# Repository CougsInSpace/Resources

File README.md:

# Getting Involved with Cougs in Space #
Cougs in Space is currently developing its first nanosatellite, **CougSat-1**, at Washington State University.

## Step One: Nanosatellites ##
* Read [Wikipedia](https://en.wikipedia.org/wiki/CubeSat)
* Read [NASA's CubeSat 101](https://github.com/CougsInSpace/Resources/blob/master/Subsystems/General/NASACubeSat101.pdf)
* Read the [CubeSat Specifications](https://github.com/CougsInSpace/Resources/blob/master/CubeSatSpecifications/CubeSatDesignSpecificationRev13.pdf)

## Step Two: Find a Team ##
Our [website](https://cis.vcea.wsu.edu/our-teams/) describes each sub team's roles. Find one that is interesting that you want to join and [let us know](https://cis.vcea.wsu.edu/new-member-application-form/).

## Step Three: Join Github ##
Don't know what Github is? [Learn here](https://guides.github.com/activities/hello-world/)

## Step Four: Check out our SOPs ##
These are the standard operating procedures within Cougs in Space:
* [Acronyms](https://github.com/CougsInSpace/Resources/blob/master/StandardOperatingProcedures/Acronyms.pdf)
* [Coding conventions](https://github.com/CougsInSpace/Resources/blob/master/StandardOperatingProcedures/Code.pdf)
* [Github](https://github.com/CougsInSpace/Resources/blob/master/StandardOperatingProcedures/GitHub.pdf)
* [Project Management](https://github.com/CougsInSpace/Resources/blob/master/StandardOperatingProcedures/ProjectManagement.pdf)
* [Units](https://github.com/CougsInSpace/Resources/blob/master/StandardOperatingProcedures/Units.pdf)

## Step Five: Start Working ##
All of our design files are located at [https://github.com/CougsInSpace](https://github.com/CougsInSpace).

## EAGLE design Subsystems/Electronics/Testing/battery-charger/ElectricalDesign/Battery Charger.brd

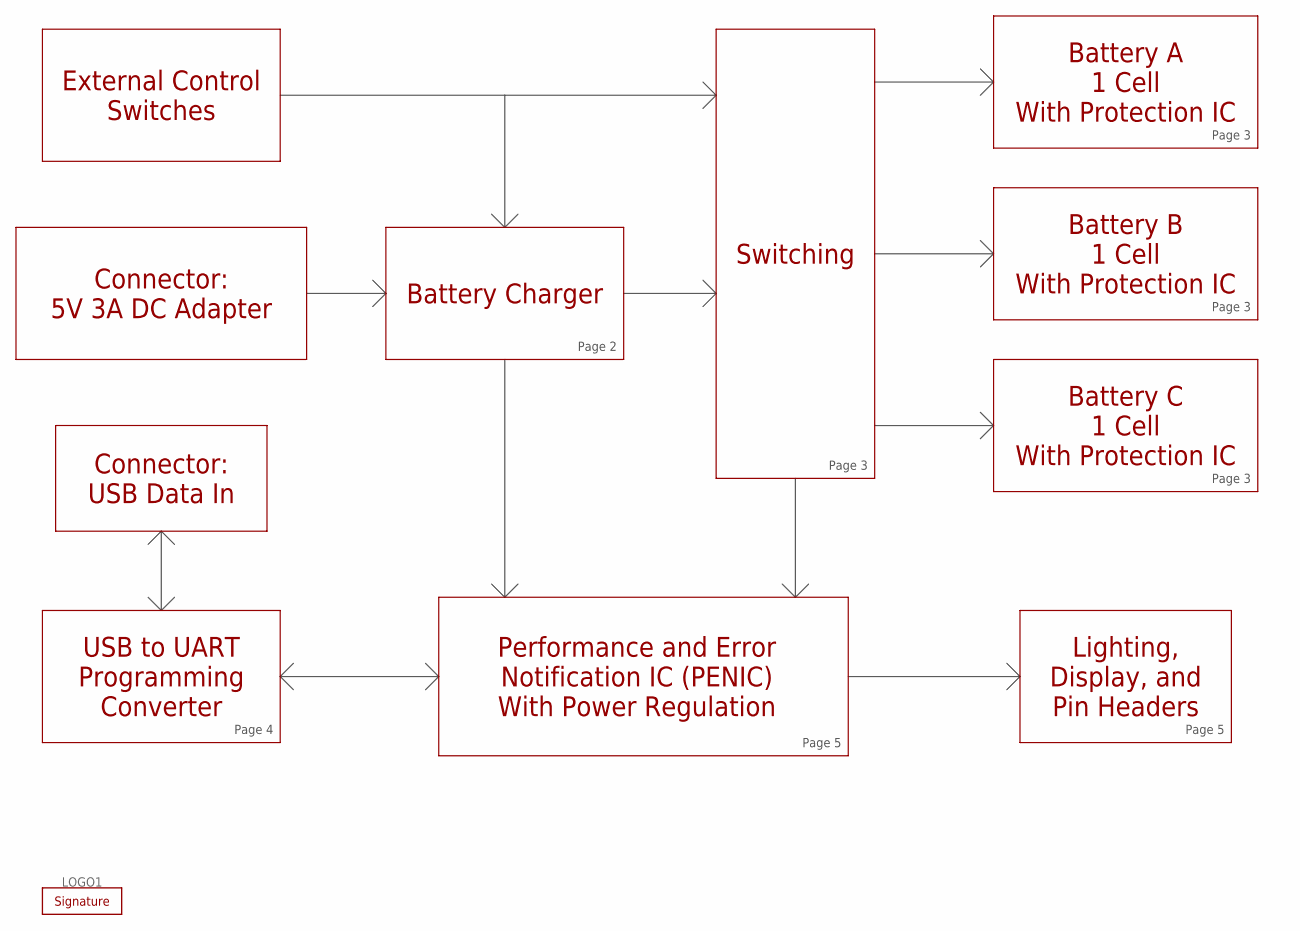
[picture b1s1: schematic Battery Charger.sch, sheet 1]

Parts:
LOGO1: SIGNATUREZACHARY; SIGN-ZACHARY

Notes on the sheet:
Connector: 5V 3A DC Adapter
Battery Charger
Switching
Battery A 1 Cell With Protection IC
Battery B 1 Cell With Protection IC
Battery C 1 Cell With Protection IC
Page 2
Page 3
Performance and Error Notification IC (PENIC) With Power Regulation
Lighting, Display, and Pin Headers
Page 5
Connector: USB Data In
USB to UART Programming Converter
Page 4
External Control Switches

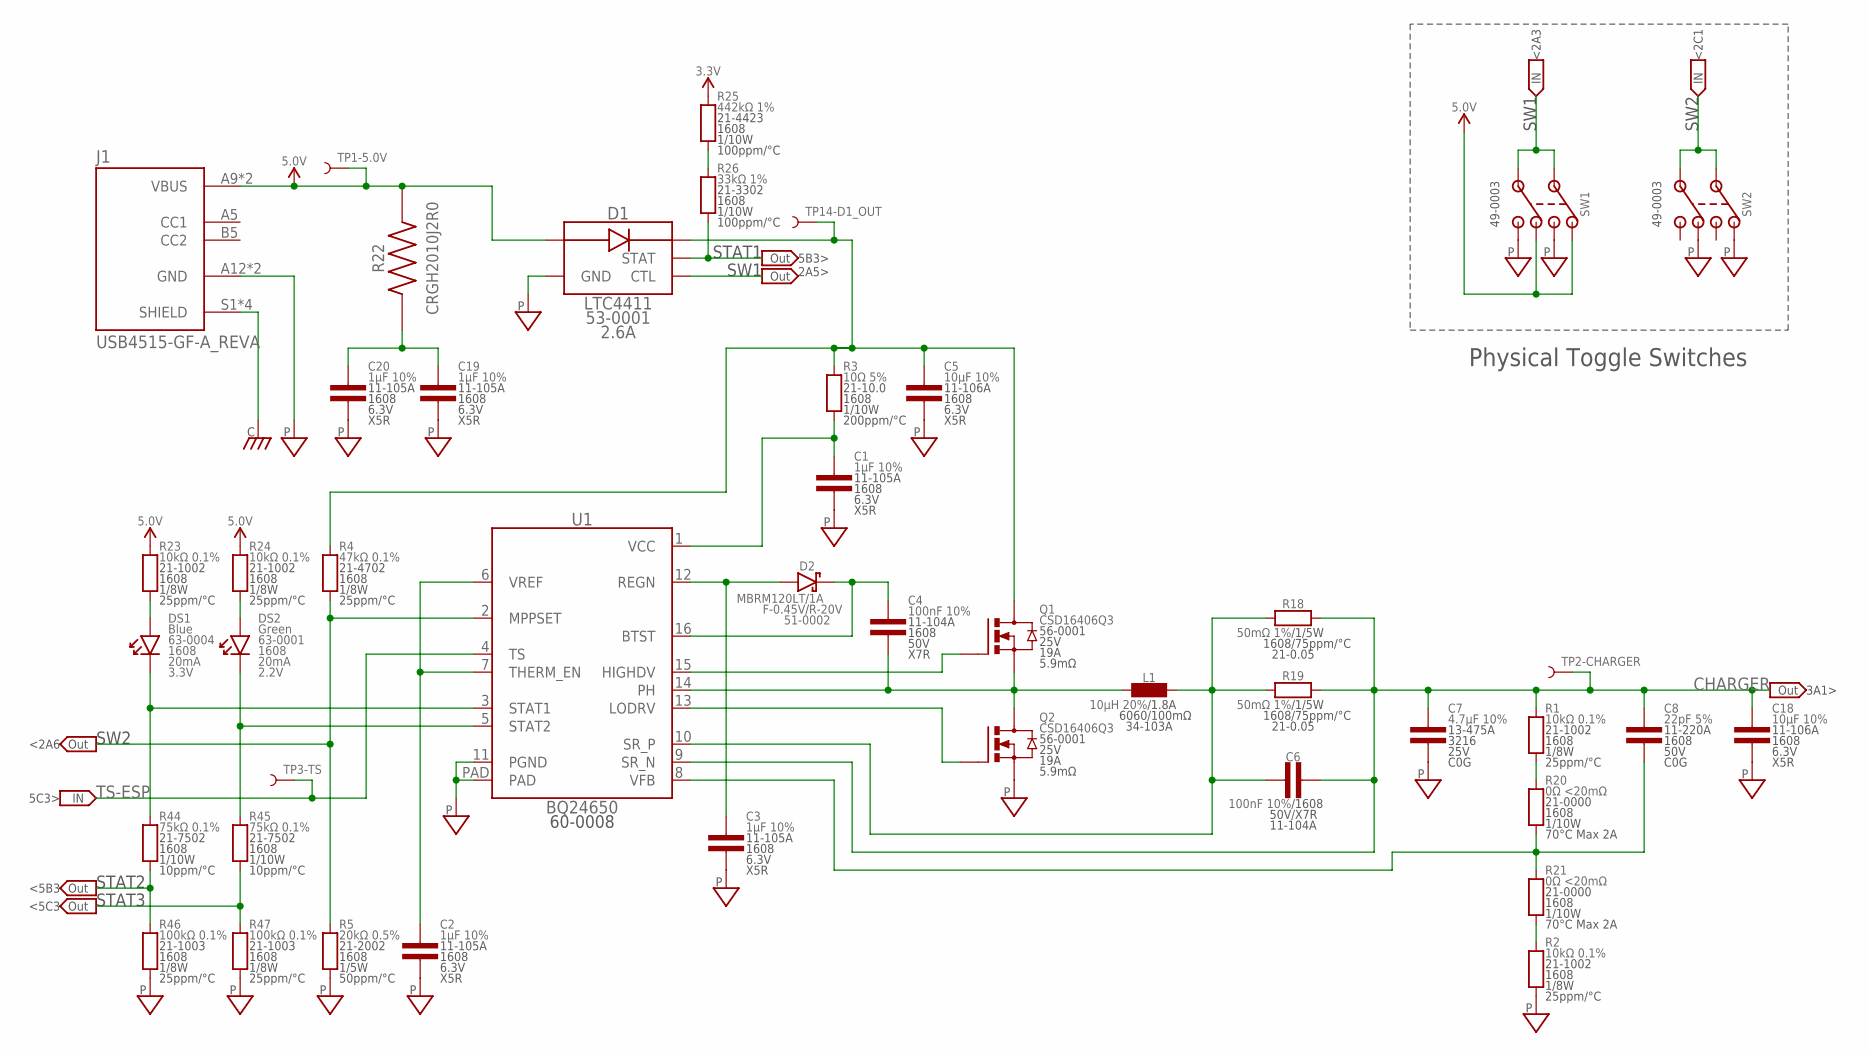
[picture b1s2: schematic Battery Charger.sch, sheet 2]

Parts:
C1, C2, C3, C19, C20: 1µF 10%; 1608
C4, C6: 100nF 10%; 1608
C5, C18: 10µF 10%; 1608
C7: 4.7µF 10%; 3216
C8: 22pF 5%; 1608
D1: LTC4411; SOT23-5
D2: MBRM120LT; POWERMITE
DS1: Blue; 1608-POL
DS2: Green; 1608-POL
J1: USB4515-GF-A_REVA; GCT_USB4515-GF-A_REVA
L1: 10µH 20%; 6060
Q1, Q2: CSD16406Q3; SON-3333
R1, R2, R23, R24: 10kΩ 0.1%; 1608
R3: 10Ω 5%; 1608
R4: 47kΩ 0.1%; 1608
R5: 20kΩ 0.5%; 1608
R18, R19: 50mΩ 1%; 1608
R20, R21: 0Ω <20mΩ; 1608
R22: CRGH2010J2R0; RESC5025X65N
R25: 442kΩ 1%; 1608
R26: 33kΩ 1%; 1608
R44, R45: 75kΩ 0.1%; 1608
R46, R47: 100kΩ 0.1%; 1608
SW1, SW2: SWITCH-DPDT-100DP1T1B1M2QE; 100DP1T1B1M2QE
TP1-5.0V, TP2-CHARGER, TP3-TS, TP14-D1_OUT: TEST_POINT-SMD-C-1.25; SMD-C-1.25
U1: BQ24650; QFN-16-3535

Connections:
3.3V: R25.2; also elsewhere on the board
5.0V: D1.1 (IN), J1.A9 (VBUS), J1.B9 (VBUS), R22.2, R23.2, R24.2, SW1.1-A, SW1.1-B, TP1-5.0V.1; also elsewhere on the board
BQ24650_BTST: C4.1, D2.C, U1.16 (BTST)
BQ24650_HIGHDV: Q1.4 (G), U1.15 (HIGHDV)
BQ24650_LODRV: Q2.4 (G), U1.13 (LODRV)
BQ24650_PH: C4.2, L1.1, Q1.1 (S), Q1.2 (S), Q1.3 (S), Q2.5 (D), Q2.6 (D), Q2.7 (D), Q2.8 (D), Q2.PAD (D), U1.14 (PH)
BQ24650_REGN: C3.1, D2.A, U1.12 (REGN)
BQ24650_SR_P: C6.1, L1.2, R18.1, R19.1, U1.10 (SR_P)
BQ24650_STAT1: DS1.C, R44.2, U1.3 (STAT1)
BQ24650_STAT2: DS2.C, R45.2, U1.5 (STAT2)
BQ24650_VCC: C1.1, R3.1, U1.1 (VCC)
BQ24650_VFB: C8.2, R20.1, R21.2, U1.8 (VFB)
BQ24650_VREF: C2.1, U1.6 (VREF), U1.7 (THERM_EN)
CHARGER: C6.2, C7.1, C8.1, C18.1, R1.2, R18.2, R19.2, TP2-CHARGER.1, U1.9 (SR_N); also elsewhere on the board
CHASSIS: J1.S1 (SHIELD), J1.S2 (SHIELD), J1.S3 (SHIELD), J1.S4 (SHIELD); also elsewhere on the board
D1_OUT: C5.1, D1.5 (OUT), Q1.5 (D), Q1.6 (D), Q1.7 (D), Q1.8 (D), Q1.PAD (D), R3.2, R4.2, TP14-D1_OUT.1
unnamed: DS1.A, R23.1
unnamed: R1.1, R20.2
unnamed: R2.2, R21.1
unnamed: DS2.A, R24.1
unnamed: C19.1, C20.1, R22.1
unnamed: R25.1, R26.2
PGND: C1.2, C2.2, C3.2, C5.2, C7.2, C18.2, C19.2, C20.2, D1.2 (GND), J1.A12 (GND), J1.B12 (GND), Q2.1 (S), Q2.2 (S), Q2.3 (S), R2.1, R5.1, R46.1, R47.1, SW1.2-A, SW1.2-B, SW2.1-A, SW2.1-B, U1.11 (PGND), U1.PAD; also elsewhere on the board
STAT1: D1.4 (STAT), R26.1; also elsewhere on the board
STAT2: R44.1, R46.2; also elsewhere on the board
STAT3: R45.1, R47.2; also elsewhere on the board
SW1: D1.3 (CTL), SW1.COM-A, SW1.COM-B
SW2: R4.1, R5.2, SW2.COM-A, SW2.COM-B, U1.2 (MPPSET)
TS-ESP: TP3-TS.1, U1.4 (TS); also elsewhere on the board

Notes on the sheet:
SW1
STAT1
SW2
STAT2
STAT3
Physical Toggle Switches
2A5>
5B3>
3A1>
<2A3
<2C1
<5B3
<5C3
5C3>
<2A6

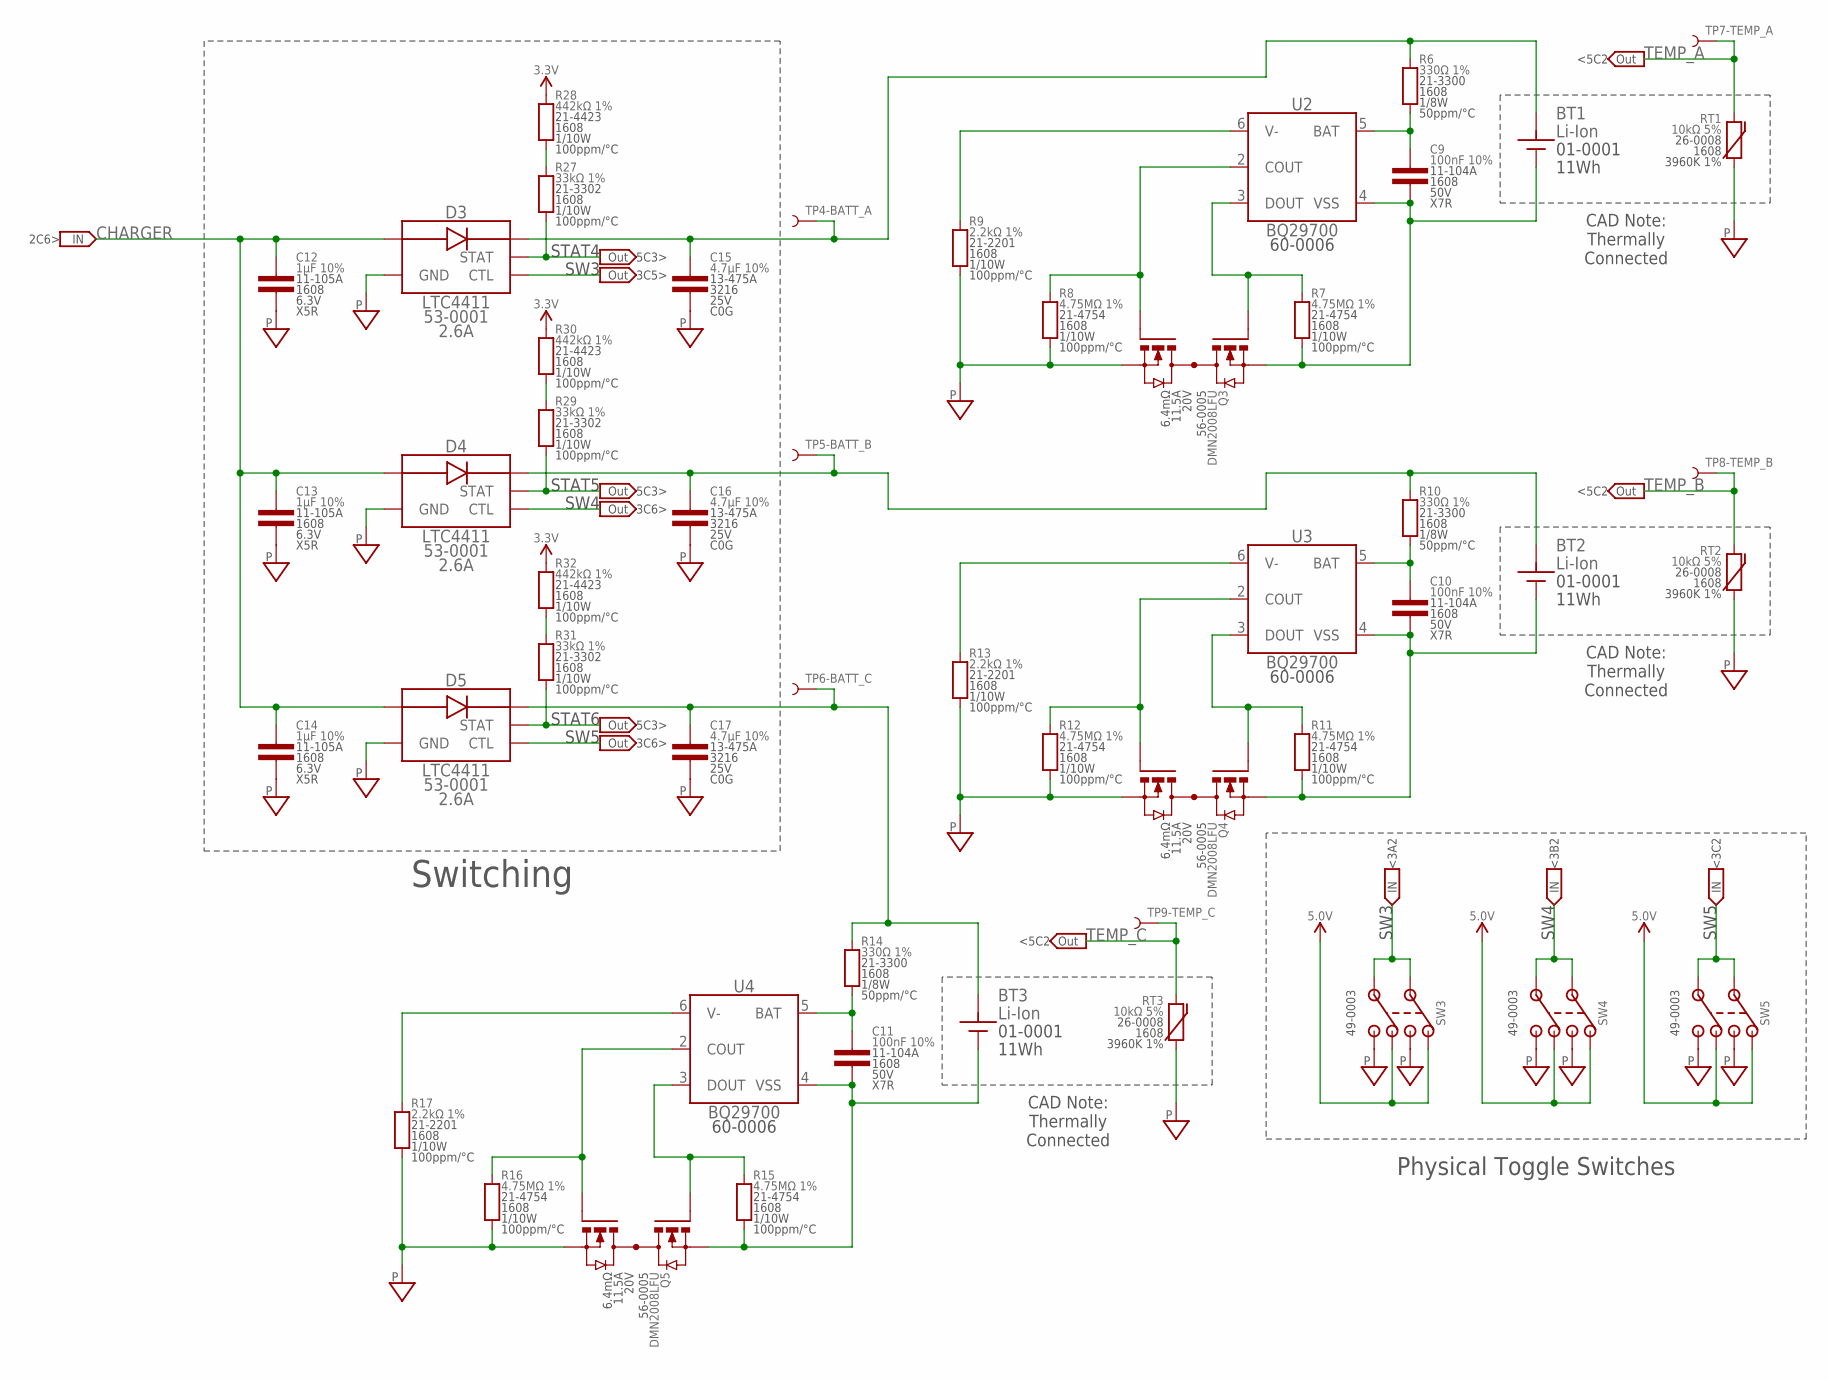
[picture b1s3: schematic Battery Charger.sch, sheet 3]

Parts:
BT1, BT2, BT3: Li-Ion; 18650-SOLDERED
C9, C10, C11: 100nF 10%; 1608
C12, C13, C14: 1µF 10%; 1608
C15, C16, C17: 4.7µF 10%; 3216
D3, D4, D5: LTC4411; SOT23-5
Q3, Q4, Q5: DMN2008LFU; UDFN-6-B
R6, R10, R14: 330Ω 1%; 1608
R7, R8, R11, R12, R15, R16: 4.75MΩ 1%; 1608
R9, R13, R17: 2.2kΩ 1%; 1608
R27, R29, R31: 33kΩ 1%; 1608
R28, R30, R32: 442kΩ 1%; 1608
RT1, RT2, RT3: 10kΩ 5%; 1608
SW3, SW4, SW5: SWITCH-DPDT-100DP1T1B1M2QE; 100DP1T1B1M2QE
TP4-BATT_A, TP5-BATT_B, TP6-BATT_C, TP7-TEMP_A, TP8-TEMP_B, TP9-TEMP_C: TEST_POINT-SMD-C-1.25; SMD-C-1.25
U2, U3, U4: BQ29700; WSON-6

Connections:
3.3V: R28.2, R30.2, R32.2; also elsewhere on the board
5.0V: SW3.1-A, SW3.1-B, SW4.1-A, SW4.1-B, SW5.1-A, SW5.1-B; also elsewhere on the board
BQ297001_BAT: C9.1, R6.1, U2.5 (BAT)
BQ297001_COUT: Q3.3 (G1), R8.2, U2.2 (COUT)
BQ297001_DOUT: Q3.4 (G2), R7.2, U2.3 (DOUT)
BQ297001_V-: R9.2, U2.6 (V-)
BQ297001_VSS: BT1.A, C9.2, Q3.6 (S2), R7.1, U2.4 (VSS)
BQ297002_BAT: C10.1, R10.1, U3.5 (BAT)
BQ297002_COUT: Q4.3 (G1), R12.2, U3.2 (COUT)
BQ297002_DOUT: Q4.4 (G2), R11.2, U3.3 (DOUT)
BQ297002_V-: R13.2, U3.6 (V-)
BQ297002_VSS: BT2.A, C10.2, Q4.6 (S2), R11.1, U3.4 (VSS)
BQ297003_BAT: C11.1, R14.1, U4.5 (BAT)
BQ297003_COUT: Q5.3 (G1), R16.2, U4.2 (COUT)
BQ297003_DOUT: Q5.4 (G2), R15.2, U4.3 (DOUT)
BQ297003_V-: R17.2, U4.6 (V-)
BQ297003_VSS: BT3.A, C11.2, Q5.6 (S2), R15.1, U4.4 (VSS)
CHARGER: C12.1, C13.1, C14.1, D3.1 (IN), D4.1 (IN), D5.1 (IN); also elsewhere on the board
D3_OUT: BT1.C, C15.1, D3.5 (OUT), R6.2, TP4-BATT_A.1
D4_OUT: BT2.C, C16.1, D4.5 (OUT), R10.2, TP5-BATT_B.1
D5_OUT: BT3.C, C17.1, D5.5 (OUT), R14.2, TP6-BATT_C.1
unnamed: R27.2, R28.1
unnamed: R29.2, R30.1
unnamed: R31.2, R32.1
PGND: C12.2, C13.2, C14.2, C15.2, C16.2, C17.2, D3.2 (GND), D4.2 (GND), D5.2 (GND), Q3.1 (S1), Q4.1 (S1), Q5.1 (S1), R8.1, R9.1, R12.1, R13.1, R16.1, R17.1, RT1.1, RT2.1, RT3.1, SW3.2-A, SW3.2-B, SW4.2-A, SW4.2-B, SW5.2-A, SW5.2-B; also elsewhere on the board
STAT4: D3.4 (STAT), R27.1; also elsewhere on the board
STAT5: D4.4 (STAT), R29.1; also elsewhere on the board
STAT6: D5.4 (STAT), R31.1; also elsewhere on the board
SW3: D3.3 (CTL), SW3.COM-A, SW3.COM-B
SW4: D4.3 (CTL), SW4.COM-A, SW4.COM-B
SW5: D5.3 (CTL), SW5.COM-A, SW5.COM-B
TEMP_A: RT1.2, TP7-TEMP_A.1; also elsewhere on the board
TEMP_B: RT2.2, TP8-TEMP_B.1; also elsewhere on the board
TEMP_C: RT3.2, TP9-TEMP_C.1; also elsewhere on the board

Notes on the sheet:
Switching
SW3
SW4
SW5
STAT4
STAT5
STAT6
Physical Toggle Switches
CAD Note: Thermally Connected
5C3>
3C5>
3C6>
<3A2
<3B2
<3C2
<5C2
2C6>

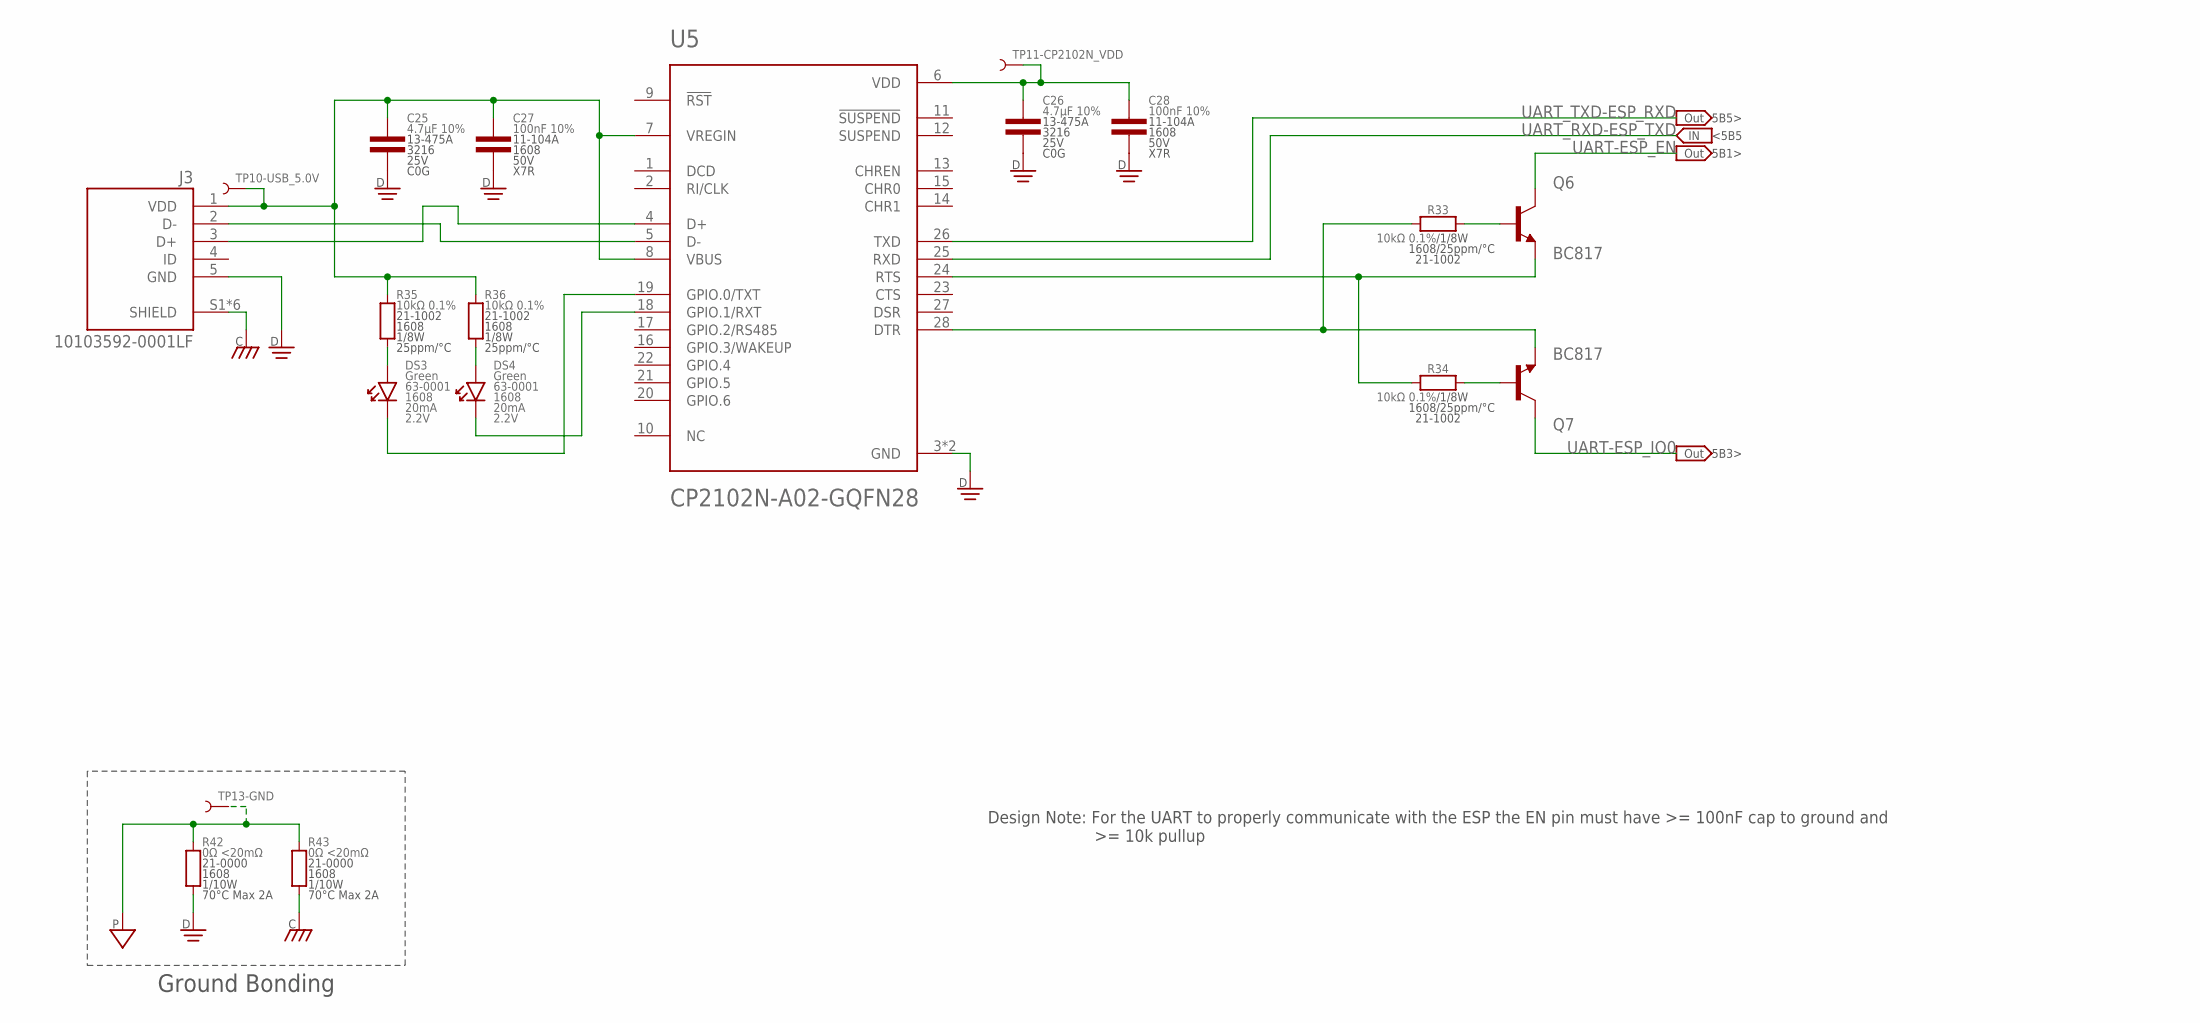
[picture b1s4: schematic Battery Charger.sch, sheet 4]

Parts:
C25, C26: 4.7µF 10%; 3216
C27, C28: 100nF 10%; 1608
DS3, DS4: Green; 1608-POL
J3: 10103592-0001LF; AMPHENOL_10103592-0001LF
Q6, Q7: BC817; SOT95P230X110-3N
R33, R34, R35, R36: 10kΩ 0.1%; 1608
R42, R43: 0Ω <20mΩ; 1608
TP10-USB_5.0V, TP11-CP2102N_VDD, TP13-GND: TEST_POINT-SMD-C-1.25; SMD-C-1.25
U5: CP2102N-A02-GQFN28; QFN50P500X500X80-29N

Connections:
CHASSIS: J3.S1 (SHIELD), J3.S2 (SHIELD), J3.S3 (SHIELD), J3.S4 (SHIELD), J3.S5 (SHIELD), J3.S6 (SHIELD), R43.1; also elsewhere on the board
CP2102N_DTR: Q7.2 (E), R33.1, U5.28 (DTR)
CP2102N_RTS: Q6.2 (E), R34.1, U5.24 (RTS)
CP2102N_RXT: DS4.C, U5.18 (GPIO.1/RXT)
CP2102N_TXT: DS3.C, U5.19 (GPIO.0/TXT)
CP2102N_VDD: C26.1, C28.1, TP11-CP2102N_VDD.1, U5.6 (VDD)
D+: J3.3 (D+), U5.4 (D+)
D-: J3.2 (D-), U5.5 (D-)
DGND: C25.2, C26.2, C27.2, C28.2, J3.5 (GND), R42.1, U5.3 (GND), U5.29 (GND)
unnamed: Q7.1 (B), R34.2
unnamed: Q6.1 (B), R33.2
unnamed: DS3.A, R35.1
unnamed: DS4.A, R36.1
PGND: R42.2, R43.2, TP13-GND.1; also elsewhere on the board
UART-ESP_EN: Q6.3 (C); also elsewhere on the board
UART-ESP_IO0: Q7.3 (C); also elsewhere on the board
UART_RXD-ESP_TXD: U5.25 (RXD); also elsewhere on the board
UART_TXD-ESP_RXD: U5.26 (TXD); also elsewhere on the board
USB_VDD: C25.1, C27.1, J3.1 (VDD), R35.2, R36.2, TP10-USB_5.0V.1, U5.7 (VREGIN), U5.8 (VBUS)

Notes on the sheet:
Design Note: For the UART to properly communicate with the ESP the EN pin must have >= 100nF cap to ground and >= 10k pullup
5B5>
<5B5
5B1>
5B3>
Ground Bonding

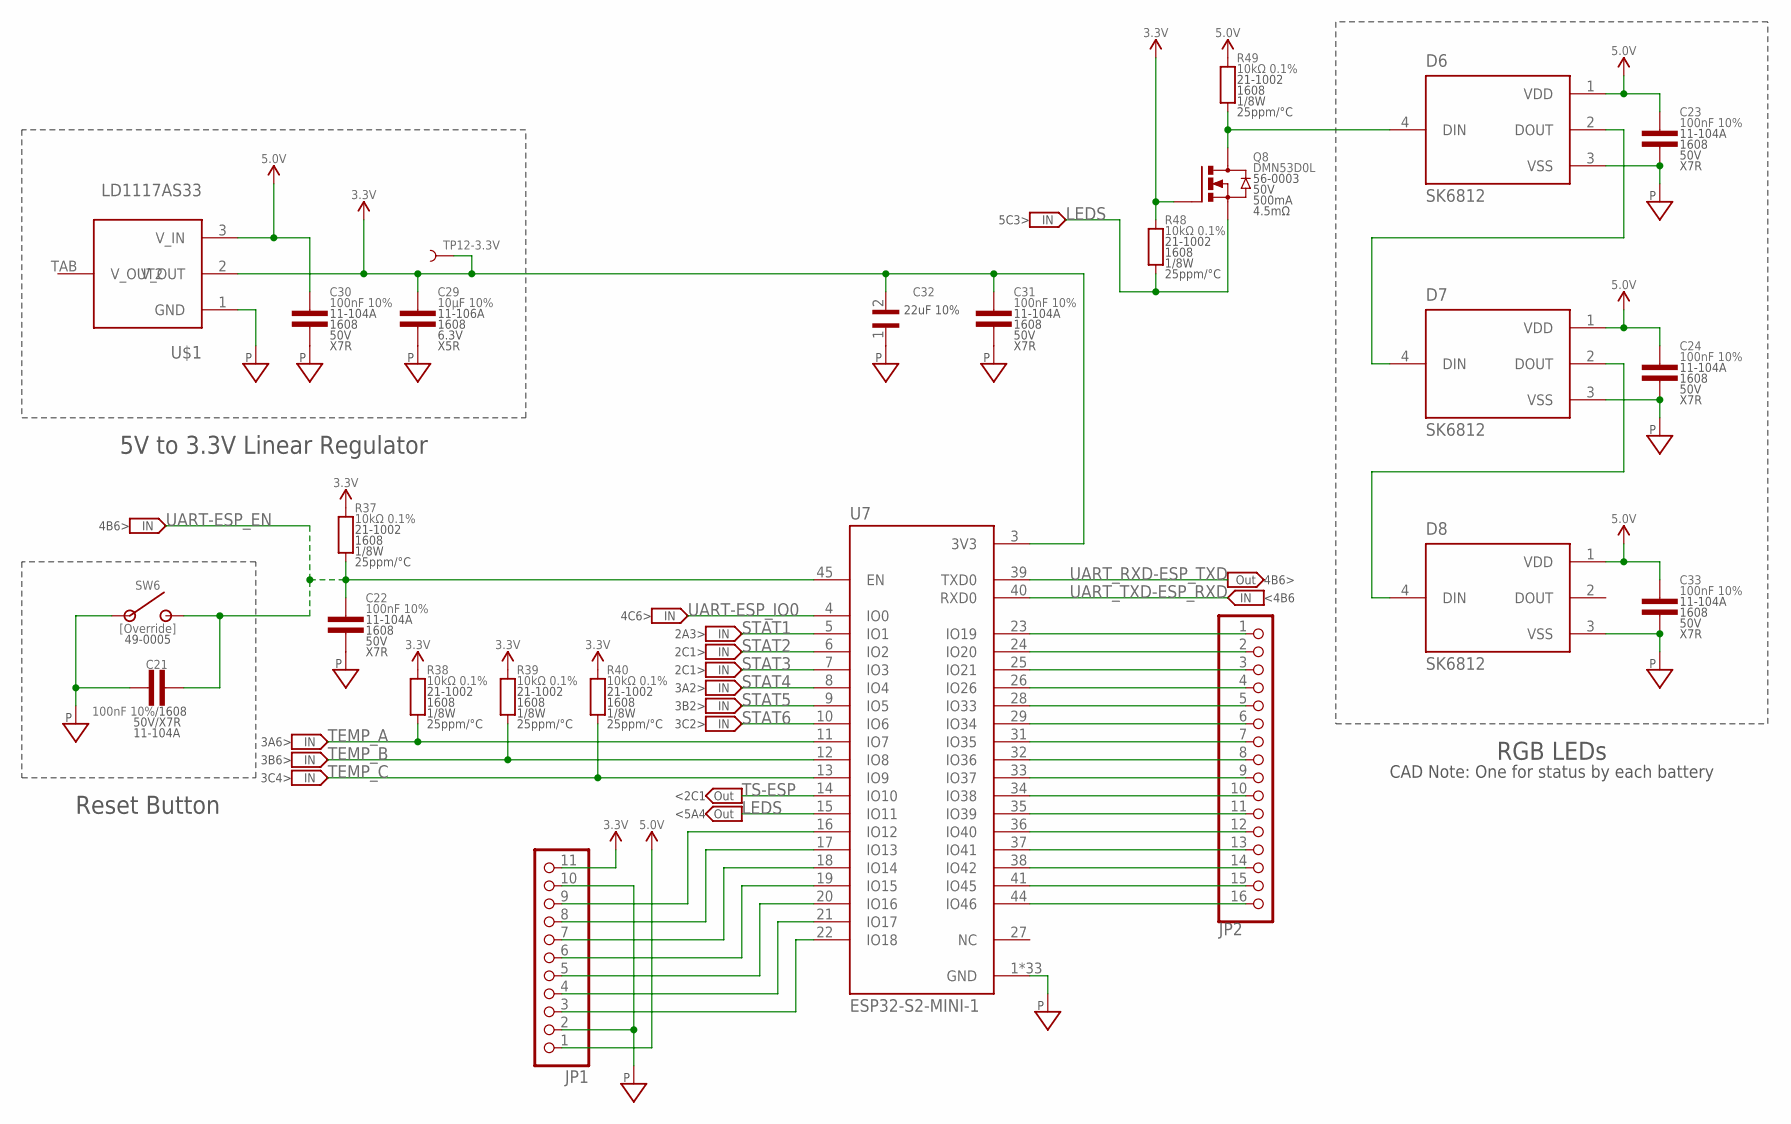
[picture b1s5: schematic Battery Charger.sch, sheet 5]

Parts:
C21, C22, C23, C24, C30, C31, C33: 100nF 10%; 1608
C29: 10µF 10%; 1608
C32: C1206C226K8RACTU; CAPC3216X110N
D6, D7, D8: SK6812; LED_SK6812
JP1: PINHD-1X11; 1X11
JP2: PINHD-1X16; 1X16
Q8: DMN53D0L; SOT23-3
R37, R38, R39, R40, R48, R49: 10kΩ 0.1%; 1608
SW6: [Override]; THT-6060
TP12-3.3V: TEST_POINT-SMD-C-1.25; SMD-C-1.25
U7: ESP32-S2-MINI-1; XCVR_ESP32-S2-MINI-1
U$1: LD1117AS33; SOT223

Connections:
3.3V: C29.1, C31.1, C32.2, JP1.11, Q8.1 (G), R37.2, R38.2, R39.2, R40.2, R48.2, TP12-3.3V.1, U7.3 (3V3), U$1.2 (V_OUT); also elsewhere on the board
5.0V: C23.1, C24.1, C30.1, C33.1, D6.1 (VDD), D7.1 (VDD), D8.1 (VDD), JP1.1, R49.2, U$1.3 (V_IN); also elsewhere on the board
ESP32_IO12: JP1.9, U7.16 (IO12)
ESP32_IO13: JP1.8, U7.17 (IO13)
ESP32_IO14: JP1.7, U7.18 (IO14)
ESP32_IO15: JP1.6, U7.19 (IO15)
ESP32_IO16: JP1.5, U7.20 (IO16)
ESP32_IO17: JP1.4, U7.21 (IO17)
ESP32_IO18: JP1.3, U7.22 (IO18)
ESP32_IO19: JP2.1, U7.23 (IO19)
ESP32_IO20: JP2.2, U7.24 (IO20)
ESP32_IO21: JP2.3, U7.25 (IO21)
ESP32_IO26: JP2.4, U7.26 (IO26)
ESP32_IO33: JP2.5, U7.28 (IO33)
ESP32_IO34: JP2.6, U7.29 (IO34)
ESP32_IO35: JP2.7, U7.31 (IO35)
ESP32_IO36: JP2.8, U7.32 (IO36)
ESP32_IO37: JP2.9, U7.33 (IO37)
ESP32_IO38: JP2.10, U7.34 (IO38)
ESP32_IO39: JP2.11, U7.35 (IO39)
ESP32_IO40: JP2.12, U7.36 (IO40)
ESP32_IO41: JP2.13, U7.37 (IO41)
ESP32_IO42: JP2.14, U7.38 (IO42)
ESP32_IO45: JP2.15, U7.41 (IO45)
ESP32_IO46: JP2.16, U7.44 (IO46)
LED1_DIN: D6.4 (DIN), Q8.3 (D), R49.1
LED2_DIN: D6.2 (DOUT), D7.4 (DIN)
LED3_DIN: D7.2 (DOUT), D8.4 (DIN)
LEDS: Q8.2 (S), R48.1, U7.15 (IO11)
PGND: C21.1, C22.2, C23.2, C24.2, C29.2, C30.2, C31.2, C32.1, C33.2, D6.3 (VSS), D7.3 (VSS), D8.3 (VSS), JP1.2, JP1.10, SW6.1 (COM), SW6.2 (COM), U7.1 (GND), U7.2 (GND), U7.30 (GND), U7.42 (GND), U7.43 (GND), U7.46 (GND), U7.47 (GND), U7.48 (GND), U7.49 (GND), U7.50 (GND), U7.51 (GND), U7.52 (GND), U7.53 (GND), U7.54 (GND), U7.55 (GND), U7.56 (GND), U7.57 (GND), U7.58 (GND), U7.59 (GND), U7.60 (GND), U7.61 (GND), U7.61_1 (GND), U7.61_2 (GND), U7.61_3 (GND), U7.61_4 (GND), U7.61_5 (GND), U7.61_6 (GND), U7.61_7 (GND), U7.61_8 (GND), U7.62 (GND), U7.63 (GND), U7.64 (GND), U7.65 (GND), U$1.1 (GND); also elsewhere on the board
STAT1: U7.5 (IO1); also elsewhere on the board
STAT2: U7.6 (IO2); also elsewhere on the board
STAT3: U7.7 (IO3); also elsewhere on the board
STAT4: U7.8 (IO4); also elsewhere on the board
STAT5: U7.9 (IO5); also elsewhere on the board
STAT6: U7.10 (IO6); also elsewhere on the board
TEMP_A: R38.1, U7.11 (IO7); also elsewhere on the board
TEMP_B: R39.1, U7.12 (IO8); also elsewhere on the board
TEMP_C: R40.1, U7.13 (IO9); also elsewhere on the board
TS-ESP: U7.14 (IO10); also elsewhere on the board
UART-ESP_EN: C21.2, C22.1, R37.1, SW6.3 (NO), SW6.4 (NO), U7.45 (EN); also elsewhere on the board
UART-ESP_IO0: U7.4 (IO0); also elsewhere on the board
UART_RXD-ESP_TXD: U7.39 (TXD0); also elsewhere on the board
UART_TXD-ESP_RXD: U7.40 (RXD0); also elsewhere on the board

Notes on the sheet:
22uF 10%
5V to 3.3V Linear Regulator
Reset Button
RGB LEDs
CAD Note: One for status by each battery
4B6>
<4B6
5C3>
3A6>
3B6>
3C4>
4C6>
2A3>
2C1>
3A2>
3B2>
3C2>
<2C1
<5A4

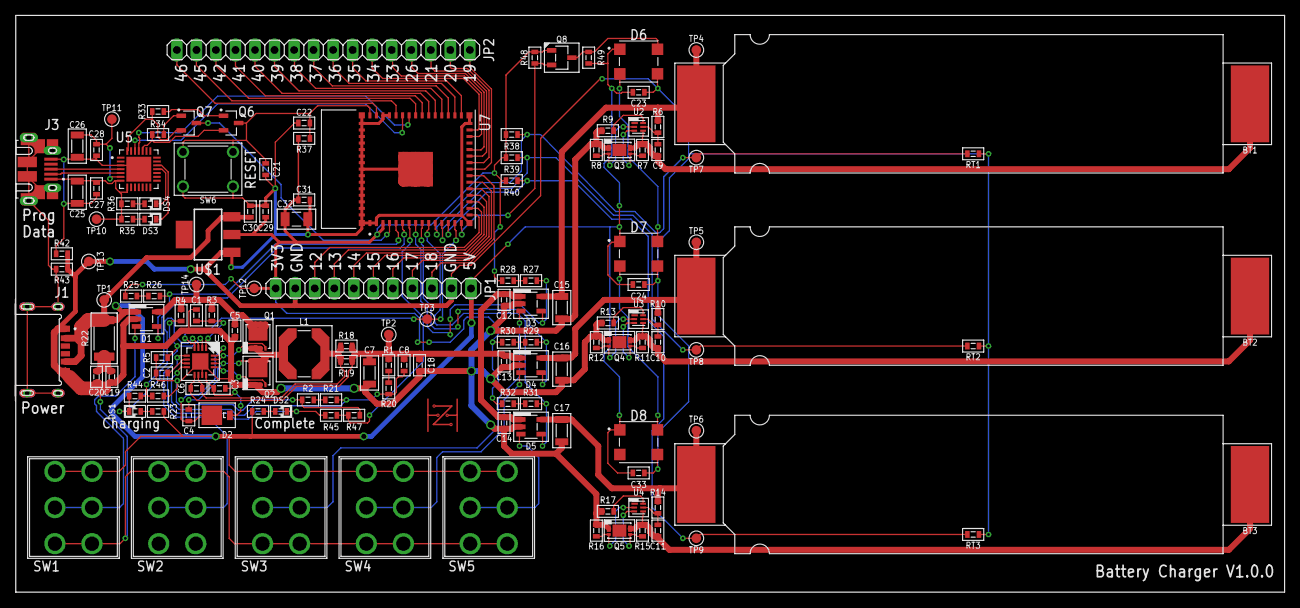
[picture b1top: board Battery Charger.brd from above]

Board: 2 copper layers, 165.1 x 75.0 mm, 140 parts (0 on the bottom side), 103 nets.

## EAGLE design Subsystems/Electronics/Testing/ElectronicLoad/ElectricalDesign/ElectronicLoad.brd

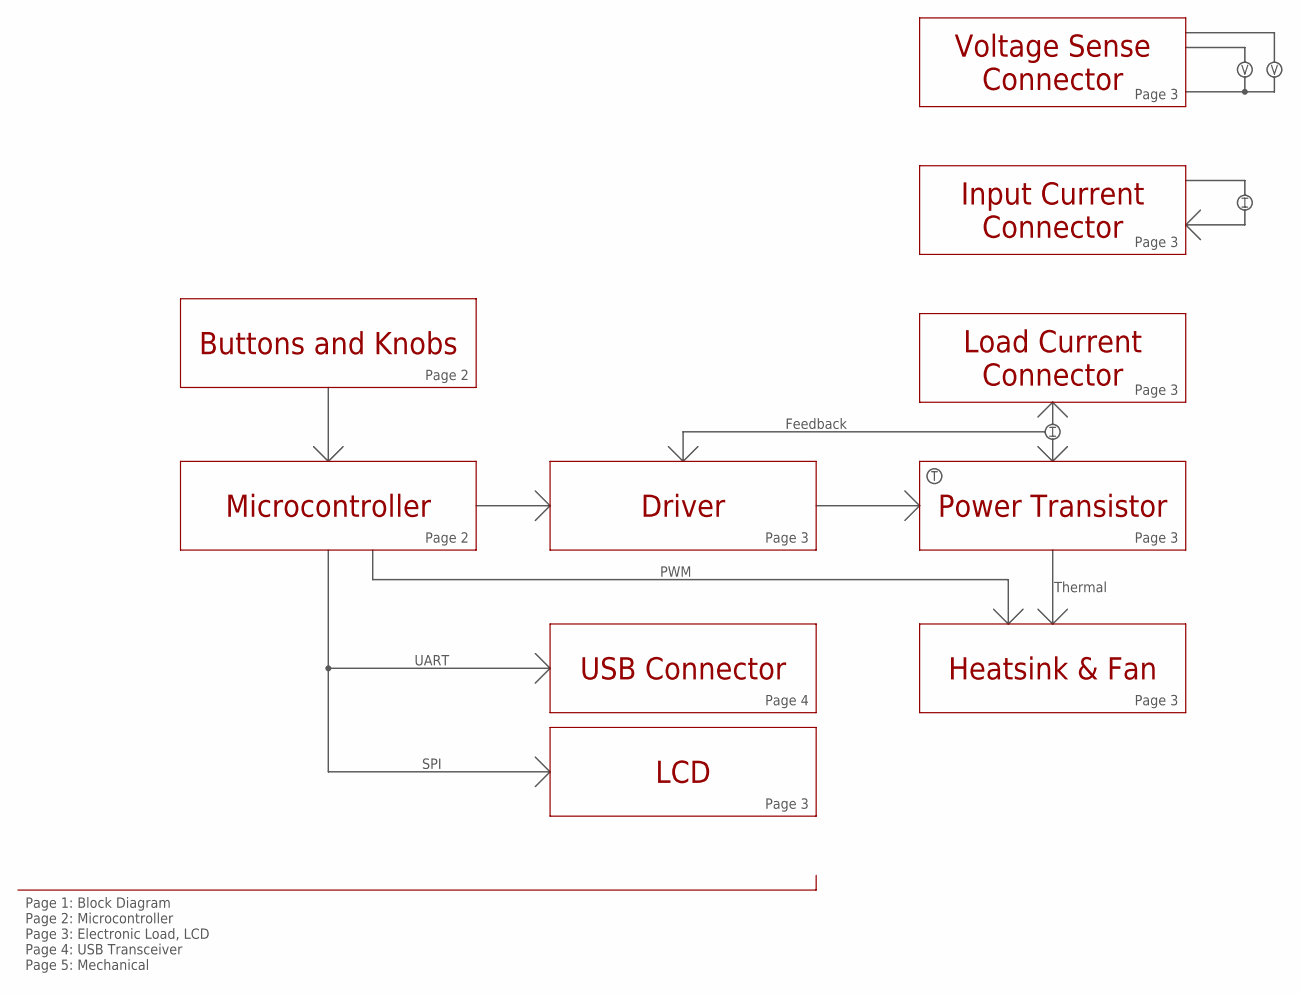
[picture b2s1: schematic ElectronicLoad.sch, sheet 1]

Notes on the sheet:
Buttons and Knobs
Page 2
Microcontroller
Power Transistor
Page 3
Load Current Connector
Driver
USB Connector
Page 4
LCD
UART
Input Current Connector
Voltage Sense Connector
Heatsink & Fan
Thermal
PWM
Feedback
Page 1: Block Diagram Page 2: Microcontroller Page 3: Electronic Load, LCD Page 4: USB Transceiver Page 5: Mechanical
SPI

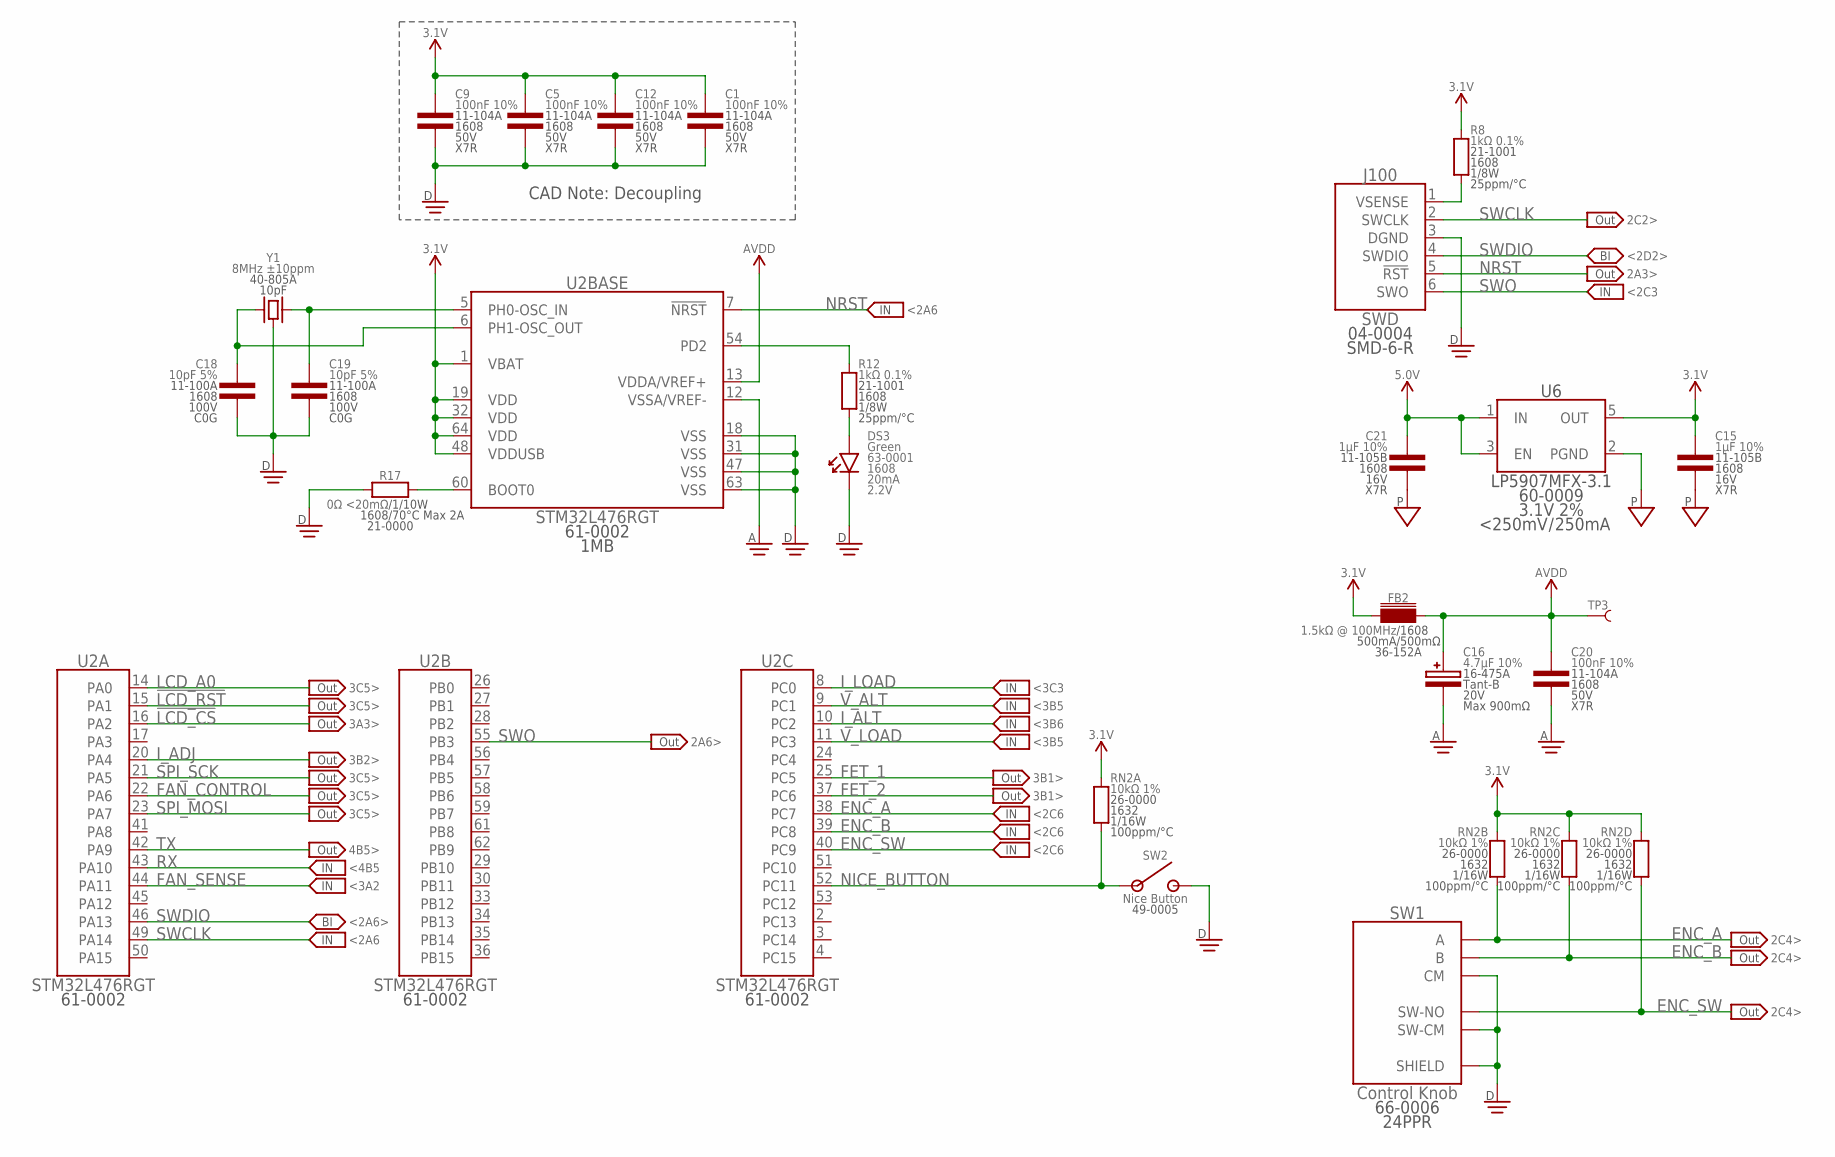
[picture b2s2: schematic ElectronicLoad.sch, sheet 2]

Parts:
C1, C5, C9, C12, C20: 100nF 10%; 1608
C15, C21: 1µF 10%; 1608
C16: 4.7µF 10%; 4028-POL
C18, C19: 10pF 5%; 1608
DS3: Green; 1608-POL
FB2: 1.5kΩ @ 100MHz; 1608
J100: SWD; SMD2.54-1X06-R
R8, R12: 1kΩ 0.1%; 1608
R17: 0Ω <20mΩ; 1608
RN2: 10kΩ 1%; 1632
SW1: Control Knob; PEC12R-4-S
SW2: Nice Button; THT-6060
TP3: TEST_POINT-SMD-C-1.25; SMD-C-1.25
U2: STM32L476RGT; QFP-64-1010
U6: LP5907MFX-3.1; SOT23-5
Y1: 8MHz ±10ppm; SMD-5032

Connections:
3.1V: C1.1, C5.1, C9.1, C12.1, C15.1, FB2.1, R8.2, RN2.5 (2), RN2.6 (2), RN2.7 (2), RN2.8 (2), U2.1 (VBAT), U2.19 (VDD), U2.32 (VDD), U2.48 (VDDUSB), U2.64 (VDD), U6.5 (OUT); also elsewhere on the board
5.0V: C21.1, U6.1 (IN), U6.3 (EN); also elsewhere on the board
!LCD_CS: U2.16 (PA2); also elsewhere on the board
!LCD_RST: U2.15 (PA1); also elsewhere on the board
AGND: C16.C, C20.2, U2.12 (VSSA/VREF-); also elsewhere on the board
AVDD: C16.A, C20.1, FB2.2, TP3.1, U2.13 (VDDA/VREF+)
BOOT0: R17.2, U2.60 (BOOT0)
DGND: C1.2, C5.2, C9.2, C12.2, C18.2, C19.2, DS3.C, J100.3 (DGND), R17.1, SW1.1 (SW-CM), SW1.C (CM), SW1.SHIELD@1 (SHIELD), SW1.SHIELD@2 (SHIELD), SW2.3 (NO), SW2.4 (NO), U2.18 (VSS), U2.31 (VSS), U2.47 (VSS), U2.63 (VSS), Y1.2 (GND), Y1.4 (GND); also elsewhere on the board
ENC_A: RN2.2 (1), SW1.A, U2.38 (PC7)
ENC_B: RN2.3 (1), SW1.B, U2.39 (PC8)
ENC_SW: RN2.4 (1), SW1.2 (SW-NO), U2.40 (PC9)
FAN_CONTROL: U2.22 (PA6); also elsewhere on the board
FAN_SENSE: U2.44 (PA11); also elsewhere on the board
FET_1: U2.25 (PC5); also elsewhere on the board
FET_2: U2.37 (PC6); also elsewhere on the board
I_ADJ: U2.20 (PA4); also elsewhere on the board
I_ALT: U2.10 (PC2); also elsewhere on the board
I_LOAD: U2.8 (PC0); also elsewhere on the board
LCD_A0: U2.14 (PA0); also elsewhere on the board
NICE_BUTTON: RN2.1, SW2.1 (COM), SW2.2 (COM), U2.52 (PC11)
NRST: J100.5 (!RST), U2.7 (!NRST)
OSC_IN: C19.1, U2.5 (PH0-OSC_IN), Y1.3 (2)
OSC_OUT: C18.1, U2.6 (PH1-OSC_OUT), Y1.1
PGND: C15.2, C21.2, U6.2 (PGND); also elsewhere on the board
RX: U2.43 (PA10); also elsewhere on the board
SPI_MOSI: U2.23 (PA7); also elsewhere on the board
SPI_SCK: U2.21 (PA5); also elsewhere on the board
SWCLK: J100.2 (SWCLK), U2.49 (PA14)
SWDIO: J100.4 (SWDIO), U2.46 (PA13)
SWO: J100.6 (SWO), U2.55 (PB3)
TO_LED: R12.2, U2.54 (EXTRA_PIN)
TO_LED_ANODE: DS3.A, R12.1
TX: U2.42 (PA9); also elsewhere on the board
VSENSE: J100.1 (VSENSE), R8.1
V_ALT: U2.9 (PC1); also elsewhere on the board
V_LOAD: U2.11 (PC3); also elsewhere on the board

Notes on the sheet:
<2A6
2A3>
2C2>
<2D2>
<2C3
<2A6>
4B5>
<4B5
3C5>
3A3>
3B2>
<3C3
<3B5
<3B6
3B1>
<2C6
2C4>
CAD Note: Decoupling
<3A2
2A6>
